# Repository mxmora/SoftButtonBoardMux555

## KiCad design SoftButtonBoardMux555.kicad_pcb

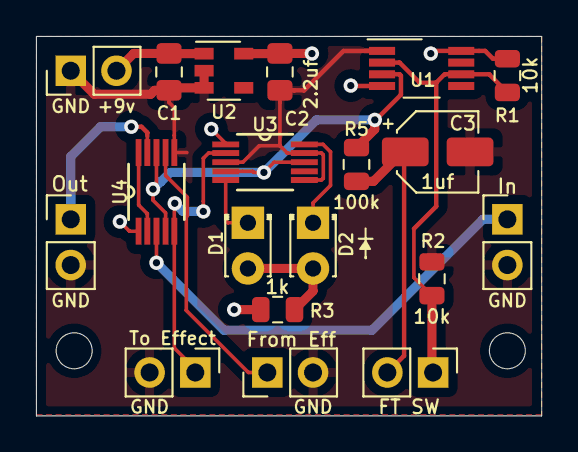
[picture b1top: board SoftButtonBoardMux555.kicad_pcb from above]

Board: 2 copper layers, 28.1 x 21.1 mm, 21 parts (0 on the bottom side), 14 nets.

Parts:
C1: 1uf; C_0805_2012Metric_Pad1.15x1.40mm_HandSolder
C2: 2.2uf; C_0805_2012Metric_Pad1.15x1.40mm_HandSolder
C3: 1uf; CP_Elec_4x3.9
D1, D2: LED; LED_D1.8mm_W3.3mm_H2.4mm
H1, H2: MountingHole; MountingHole_2mm
J1, J5: IN_OUT; PinHeader_1x02_P2.54mm_Vertical
J2: FT SW; PinHeader_1x02_P2.54mm_Vertical
J3, J6: EFF_IN_OUT; PinHeader_1x02_P2.54mm_Vertical
J4: PWR_IN; PinHeader_1x02_P2.54mm_Vertical
R1, R2: 10k; R_0805_2012Metric
R3: 1k; R_0805_2012Metric
R5: 100k; R_0805_2012Metric
U1: NE555DR; VSSOP-8_3.0x3.0mm_P0.65mm
U2: AP2204K-5.0; SOT-23-5
U3, U4: ADG884BRMZ; SOP50P490X110-10N

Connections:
+9V: C1.1, J4.2, U2.1
FromEffect: J3.1, U4.7
GND: C1.2, C2.2, C3.2, J1.2, J3.2, J4.1, J5.2, J6.2, R2.2, U1.1, U2.2, U2.3, U3.3, U3.6, U3.9, U4.6
Input: J5.1, U4.3
unnamed: C3.1, J2.2, R5.2
unnamed: D1.1, U3.5
unnamed: D1.2, D2.2, R3.1
unnamed: D2.1, U3.10
unnamed: J2.1, R1.1, R2.1, U1.2, U1.6
unnamed: U4.2, U4.10
ON_SIG: R5.1, U1.3, U3.4, U3.8, U4.4, U4.8
Output: J1.1, U4.9
ToEffect: J6.1, U3.2, U4.5
Vcc: C2.1, R1.2, R3.2, U1.4, U1.8, U2.5, U3.1, U4.1

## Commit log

2019-11-10 fix switch connection
2019-11-13 Switch to new LDO reduce the size and add better connection points
